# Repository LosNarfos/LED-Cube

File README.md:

# LED-Cube
RGB led cube with 8x8x8 size. 

Testing

http://de.farnell.com/mean-well/lrs-100-5/netzteil-ac-dc-5v-18a/dp/2815972?st=Meanwell
http://de.farnell.com/infineon/irf7410gtrpbf/mosfet-p-kanal-12v-16a-soic/dp/2725904?st=IRF7410GTRPBF
http://de.farnell.com/texas-instruments/tlc5916id/led-treiber-linear-16-soic/dp/1755247?st=TLC591

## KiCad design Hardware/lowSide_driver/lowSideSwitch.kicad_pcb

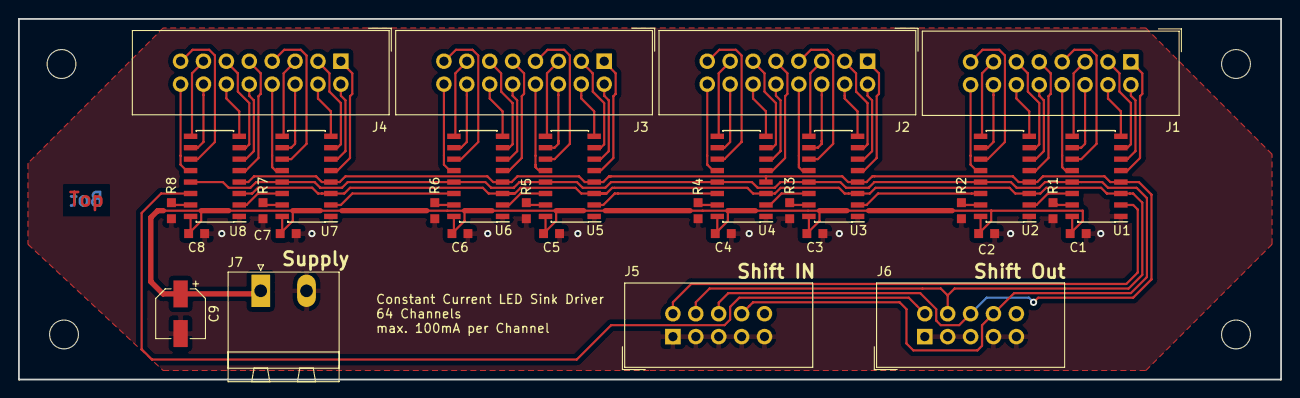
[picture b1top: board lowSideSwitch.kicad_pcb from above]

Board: 2 copper layers, 140.0 x 40.0 mm, 32 parts (0 on the bottom side), 86 nets.

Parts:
C1, C2, C3, C4, C5, C6, C7, C8: 0.1u; C_0603_1608Metric_Pad0.99x1.00mm_HandSolder
C9: CP; CP_Elec_5x5.9
J1: LEDS_0-15; IDC-Header_2x08_P2.54mm_Vertical
J2, J3, J4: Conn_01x16; IDC-Header_2x08_P2.54mm_Vertical
J5, J6: Conn_01x10; IDC-Header_2x05_P2.54mm_Vertical
J7: Conn_01x02; PhoenixContact_MSTBA_2,5_2-G-5,08_1x02_P5.08mm_Horizontal
R1, R2, R3, R4, R5, R6, R7, R8: 120; R_0603_1608Metric_Pad0.99x1.00mm_HandSolder
U1, U2, U3, U4, U5, U6, U7, U8: TLC591; SOIC-16_3.9x9.9mm_P1.27mm

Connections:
/SDI: J5.2, U1.2
/SDO: J6.2, U8.14
CLK: J5.4, J6.4, U1.3, U2.3, U3.3, U4.3, U5.3, U6.3, U7.3, U8.3
GND: C1.2, C2.2, C3.2, C4.2, C5.2, C6.2, C7.2, C8.2, C9.2, J5.1, J5.3, J5.5, J5.7, J5.9, J6.1, J6.3, J6.5, J6.7, J6.9, J7.2, R1.1, R2.1, R3.1, R4.1, R5.1, R6.1, R7.1, R8.1, U1.1, U2.1, U3.1, U4.1, U5.1, U6.1, U7.1, U8.1
LE: J5.6, J6.6, U1.4, U2.4, U3.4, U4.4, U5.4, U6.4, U7.4, U8.4
LED_0: J1.1, U1.5
LED_1: J1.2, U1.6
LED_2: J1.3, U1.7
LED_3: J1.4, U1.8
LED_4: J1.5, U1.9
LED_5: J1.6, U1.10
LED_6: J1.7, U1.11
LED_7: J1.8, U1.12
LED_8: J1.9, U2.5
LED_9: J1.10, U2.6
LED_10: J1.11, U2.7
LED_11: J1.12, U2.8
LED_12: J1.13, U2.9
LED_13: J1.14, U2.10
LED_14: J1.15, U2.11
LED_15: J1.16, U2.12
LED_16: J2.1, U3.5
LED_17: J2.2, U3.6
LED_18: J2.3, U3.7
LED_19: J2.4, U3.8
LED_20: J2.5, U3.9
LED_21: J2.6, U3.10
LED_22: J2.7, U3.11
LED_23: J2.8, U3.12
LED_24: J2.9, U4.5
LED_25: J2.10, U4.6
LED_26: J2.11, U4.7
LED_27: J2.12, U4.8
LED_28: J2.13, U4.9
LED_29: J2.14, U4.10
LED_30: J2.15, U4.11
LED_31: J2.16, U4.12
LED_32: J3.1, U5.5
LED_33: J3.2, U5.6
LED_34: J3.3, U5.7
LED_35: J3.4, U5.8
LED_36: J3.5, U5.9
LED_37: J3.6, U5.10
LED_38: J3.7, U5.11
LED_39: J3.8, U5.12
LED_40: J3.9, U6.5
LED_41: J3.10, U6.6
LED_42: J3.11, U6.7
LED_43: J3.12, U6.8
LED_44: J3.13, U6.9
LED_45: J3.14, U6.10
LED_46: J3.15, U6.11
LED_47: J3.16, U6.12
LED_48: J4.1, U7.5
LED_49: J4.2, U7.6
LED_50: J4.3, U7.7
LED_51: J4.4, U7.8
LED_52: J4.5, U7.9
LED_53: J4.6, U7.10
LED_54: J4.7, U7.11
LED_55: J4.8, U7.12
LED_56: J4.9, U8.5
LED_57: J4.10, U8.6
LED_58: J4.11, U8.7
LED_59: J4.12, U8.8
LED_60: J4.13, U8.9
LED_61: J4.14, U8.10
LED_62: J4.15, U8.11
LED_63: J4.16, U8.12
unnamed: R1.2, U1.15
unnamed: R2.2, U2.15
unnamed: R3.2, U3.15
unnamed: R4.2, U4.15
unnamed: R5.2, U5.15
unnamed: R6.2, U6.15
unnamed: R7.2, U7.15
unnamed: R8.2, U8.15
unnamed: U1.14, U2.2
unnamed: U2.14, U3.2
unnamed: U3.14, U4.2
unnamed: U4.14, U5.2
unnamed: U5.14, U6.2
unnamed: U6.14, U7.2
unnamed: U7.14, U8.2
OE: J5.8, J6.8, U1.13, U2.13, U3.13, U4.13, U5.13, U6.13, U7.13, U8.13
VCC: C1.1, C2.1, C3.1, C4.1, C5.1, C6.1, C7.1, C8.1, C9.1, J7.1, U1.16, U2.16, U3.16, U4.16, U5.16, U6.16, U7.16, U8.16

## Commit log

2018-05-07 initial project version
2018-05-07 Testing commiting to github repo
2018-05-07 Still testing
2018-05-07 Adding FirstTest-Files for STM32F4discovery with CMSIS Only CMSIS files, no extra libraries or macros (bare metal) Includes: - Makefile customized for project structure - clock frequncy set through s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
2018-05-09 Restructuring folder hierachy - Hardware - lowSide_driver PCB wit how side LED driver, for a single layer of 64 LEDs - highSide_driver PCB with high side LED driver, for multiplexing the 8 layers - d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
2018-05-13 Non-feture update, debugging
    - Added LED driver code
    - Simple shifting out data to driver ics
    - Added PWM-function for single LED
    - Added HighSide-Driver schematic
2018-05-23 PCB design of highside-multiplexer and lowside-switch - New KiCad Lib in Hardware folder
2019-02-26 Software: Added timer for LE and OE
2019-02-28 LED DMA called by own timer now
2019-03-04 Added new LowSide Board.
2019-03-05 Added pcb-file for lowSide Driver
